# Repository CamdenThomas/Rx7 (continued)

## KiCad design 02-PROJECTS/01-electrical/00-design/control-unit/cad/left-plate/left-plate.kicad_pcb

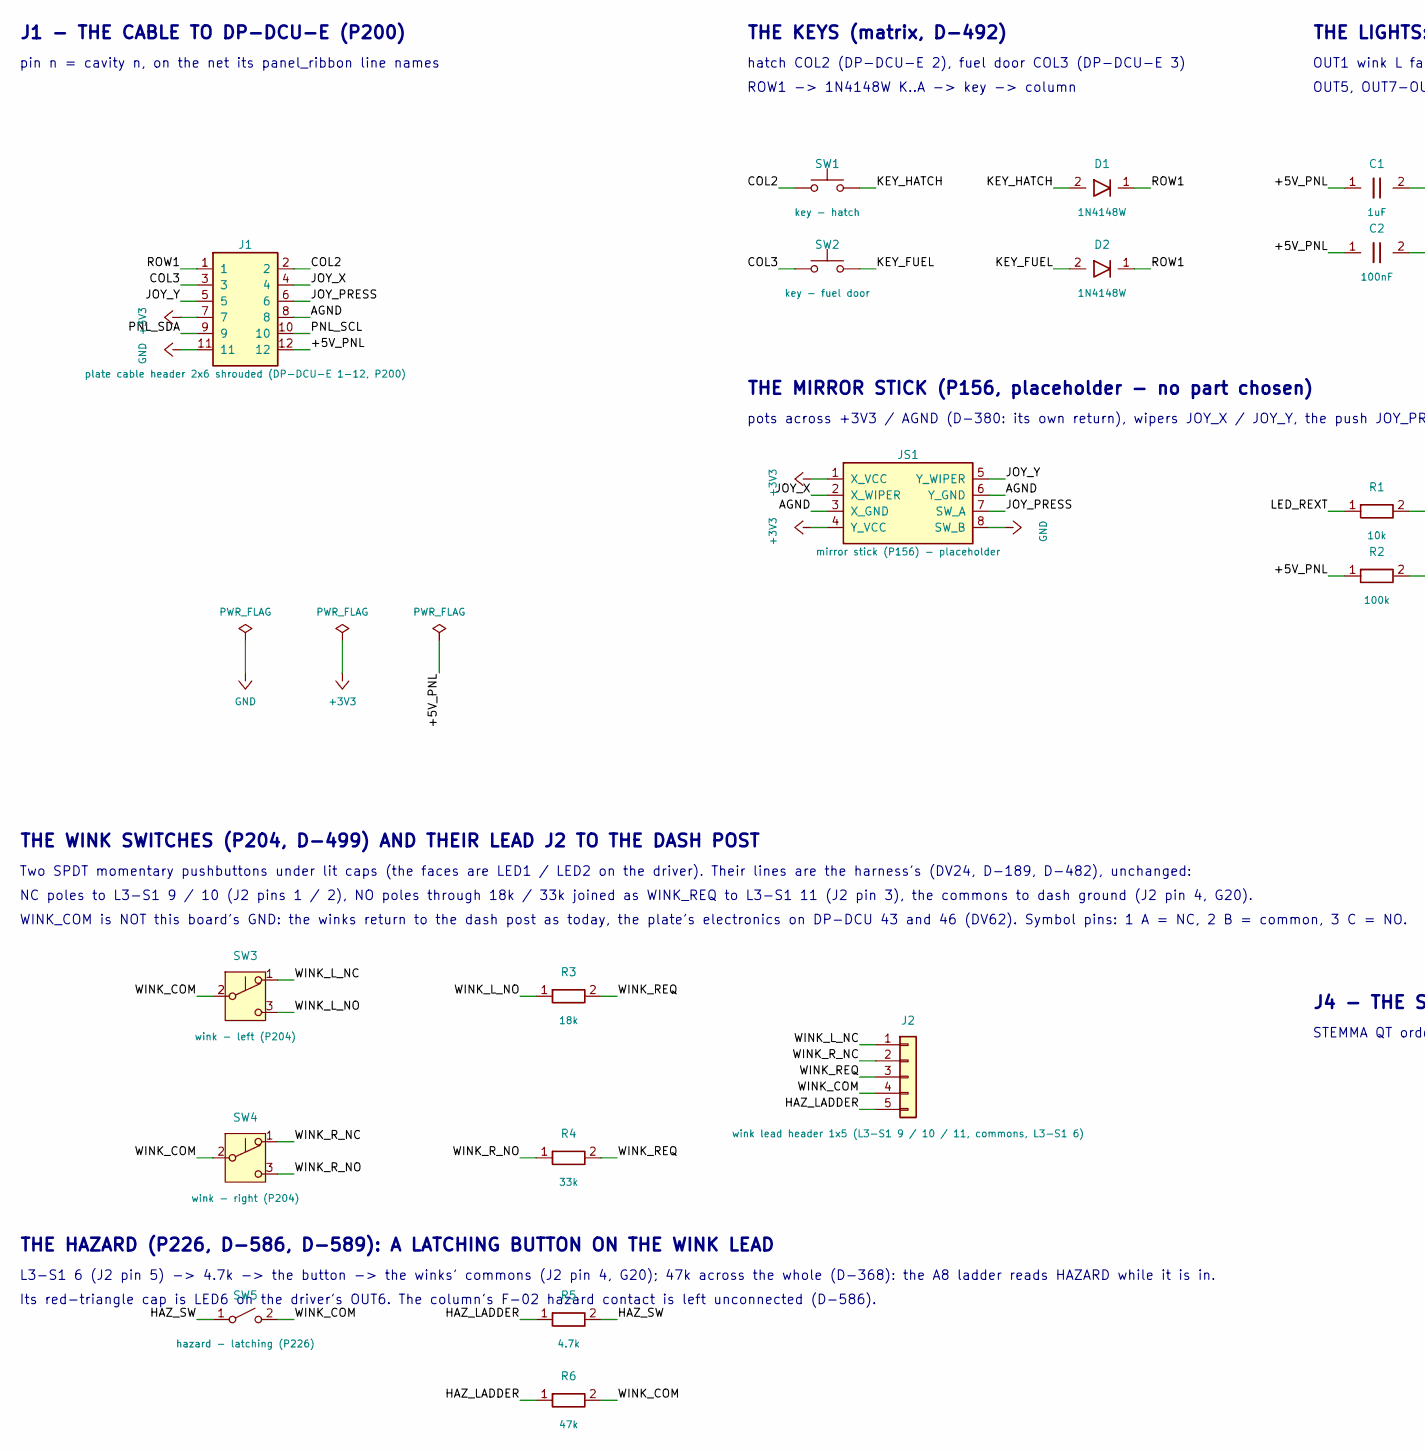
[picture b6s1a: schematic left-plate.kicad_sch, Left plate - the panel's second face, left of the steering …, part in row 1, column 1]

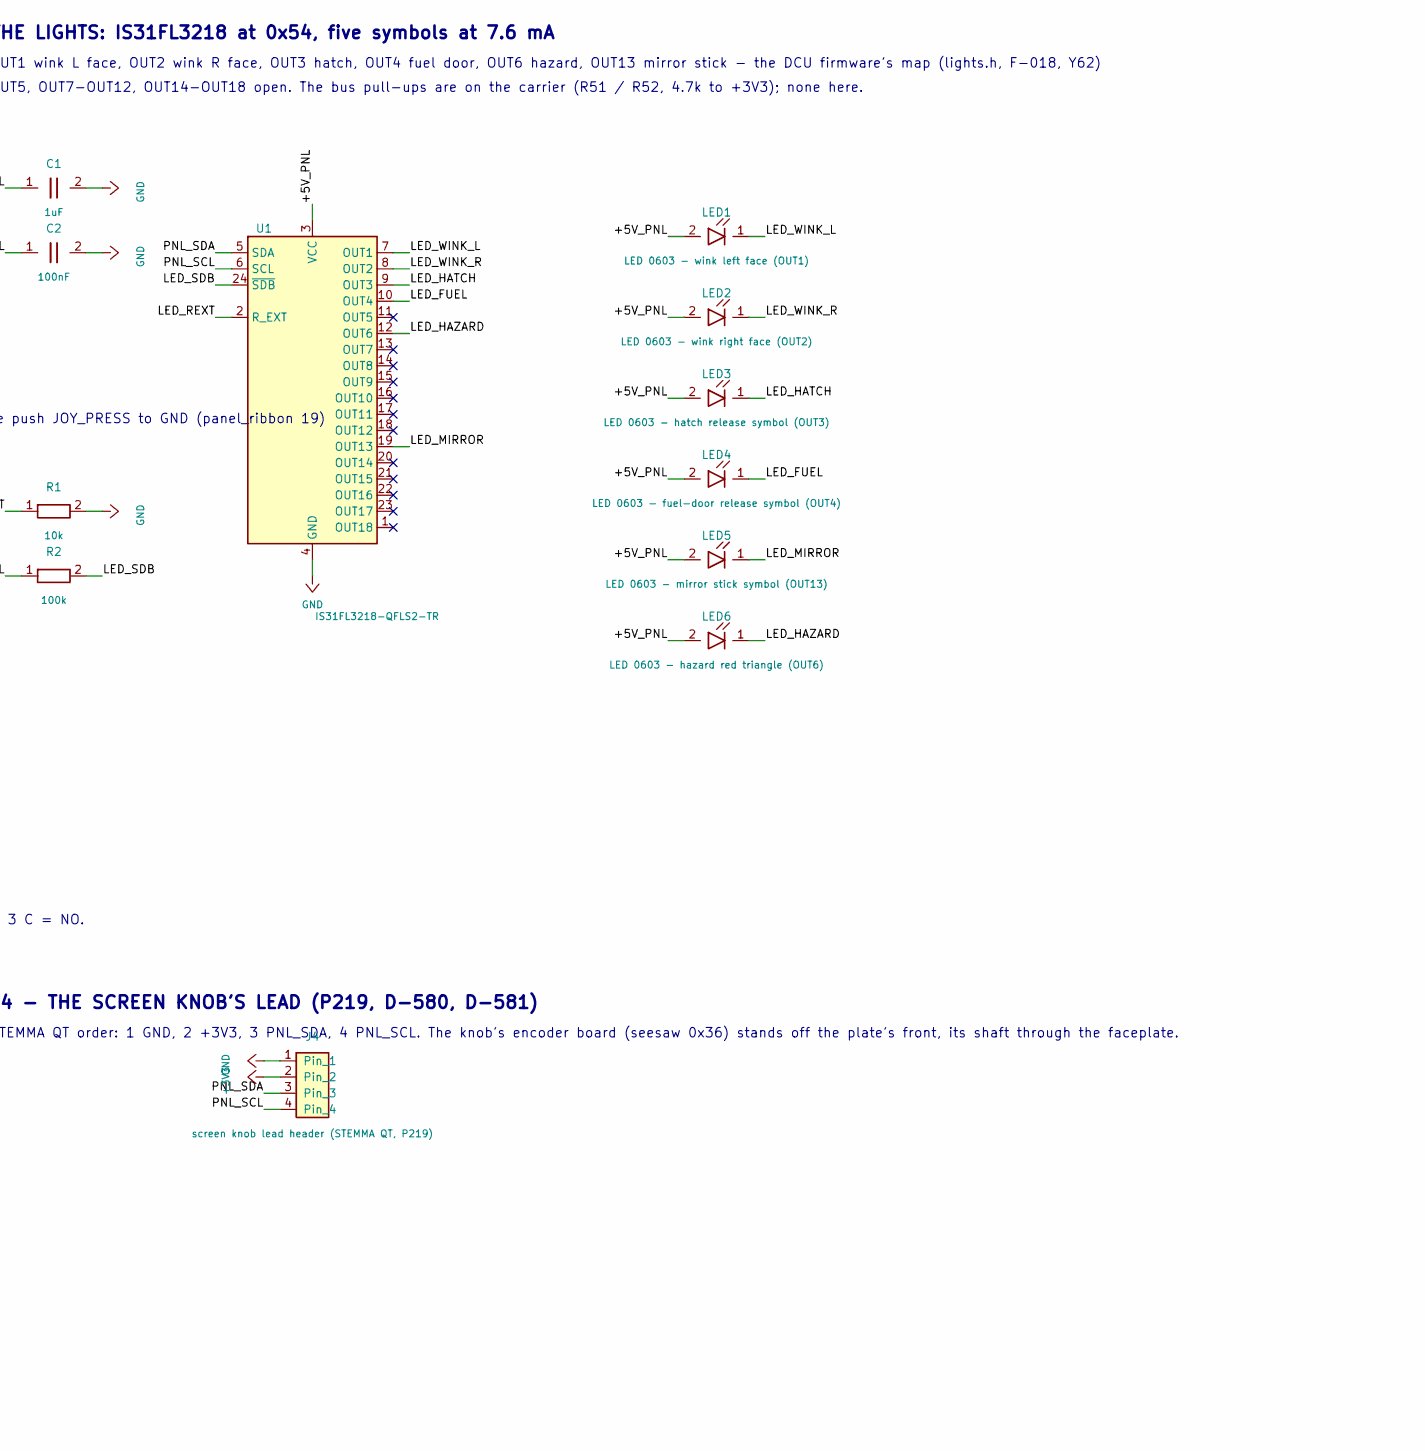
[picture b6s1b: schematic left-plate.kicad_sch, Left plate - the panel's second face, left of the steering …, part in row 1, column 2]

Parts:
C1: 1uF; C_0603_1608Metric
C2: 100nF; C_0603_1608Metric
D1, D2: 1N4148W; D_SOD-123
J1: plate cable header 2x6 shrouded (DP-DCU-E 1-12, P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; IDC-Header_2x06_P2.54mm_Vertical
J2: wink lead header 1x5 (L3-S1 9 / 10 / 11, commons,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; JST_XH_B5B-XH-A_1x05_P2.50mm_Vertical
J4: screen knob lead header (STEMMA QT, P219); JST_SH_BM04B-SRSS-TB_1x04-1MP_P1.00mm_Vertical
JS1: mirror stick (P156) - placeholder; Thumbstick_P156_Placeholder_2x04_P2.54mm
LED1: LED 0603 - wink left face (OUT1); LED_0603_1608Metric
LED2: LED 0603 - wink right face (OUT2); LED_0603_1608Metric
LED3: LED 0603 - hatch release symbol (OUT3); LED_0603_1608Metric
LED4: LED 0603 - fuel-door release symbol (OUT4); LED_0603_1608Metric
LED5: LED 0603 - mirror stick symbol (OUT13); LED_0603_1608Metric
LED6: LED 0603 - hazard red triangle (OUT6); LED_0603_1608Metric
R1: 10k; R_0603_1608Metric
R2: 100k; R_0603_1608Metric
R3: 18k; R_0603_1608Metric
R4: 33k; R_0603_1608Metric
R5: 4.7k; R_0603_1608Metric
R6: 47k; R_0603_1608Metric
SW1: key - hatch; SW_PUSH_6mm
SW2: key - fuel door; SW_PUSH_6mm
SW3: wink - left (P204); WinkSwitch_P204_SPDT_Placeholder
SW4: wink - right (P204); WinkSwitch_P204_SPDT_Placeholder
SW5: hazard - latching (P226); HazardSwitch_P226_Latching_Placeholder
U1: IS31FL3218-QFLS2-TR; QFN-24-1EP_4x4mm_P0.5mm_EP2.7x2.7mm

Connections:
+3V3: J1.7, J4.2, JS1.1 (X_VCC), JS1.4 (Y_VCC)
/+5V_PNL: C1.1, C2.1, J1.12, LED1.2 (A), LED2.2 (A), LED3.2 (A), LED4.2 (A), LED5.2 (A), LED6.2 (A), R2.1, U1.3 (VCC)
/AGND: J1.8, JS1.3 (X_GND), JS1.6 (Y_GND)
/COL2: J1.2, SW1.1
/COL3: J1.3, SW2.1
/HAZ_LADDER: J2.5, R5.1, R6.1
/HAZ_SW: R5.2, SW5.1 (A)
/JOY_PRESS: J1.6, JS1.7 (SW_A)
/JOY_X: J1.4, JS1.2 (X_WIPER)
/JOY_Y: J1.5, JS1.5 (Y_WIPER)
/KEY_FUEL: D2.2 (A), SW2.2
/KEY_HATCH: D1.2 (A), SW1.2
/LED_FUEL: LED4.1 (K), U1.10 (OUT4)
/LED_HATCH: LED3.1 (K), U1.9 (OUT3)
/LED_HAZARD: LED6.1 (K), U1.12 (OUT6)
/LED_MIRROR: LED5.1 (K), U1.19 (OUT13)
/LED_REXT: R1.1, U1.2 (R_EXT)
/LED_SDB: R2.2, U1.24 (~SDB)
/LED_WINK_L: LED1.1 (K), U1.7 (OUT1)
/LED_WINK_R: LED2.1 (K), U1.8 (OUT2)
/PNL_SCL: J1.10, J4.4, U1.6 (SCL)
/PNL_SDA: J1.9, J4.3, U1.5 (SDA)
/ROW1: D1.1 (K), D2.1 (K), J1.1
/WINK_COM: J2.4, R6.2, SW3.2 (B), SW4.2 (B), SW5.2 (B)
/WINK_L_NC: J2.1, SW3.1 (A)
/WINK_L_NO: R3.1, SW3.3 (C)
/WINK_REQ: J2.3, R3.2, R4.2
/WINK_R_NC: J2.2, SW4.1 (A)
/WINK_R_NO: R4.1, SW4.3 (C)
GND: C1.2, C2.2, J1.11, J4.1, JS1.8 (SW_B), R1.2, U1.4 (GND), U1.25 (GND)

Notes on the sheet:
J1 - THE CABLE TO DP-DCU-E (P200)
pin n = cavity n, on the net its panel_ribbon line names
THE KEYS (matrix, D-492)
ROW1 -> 1N4148W K..A -> key -> column
hatch COL2 (DP-DCU-E 2), fuel door COL3 (DP-DCU-E 3)
THE MIRROR STICK (P156, placeholder - no part chosen)
pots across +3V3 / AGND (D-380: its own return), wipers JOY_X / JOY_Y, the push JOY_PRESS to GND (panel_ribbon 19)
THE LIGHTS: IS31FL3218 at 0x54, five symbols at 7.6 mA
OUT1 wink L face, OUT2 wink R face, OUT3 hatch, OUT4 fuel door, OUT6 hazard, OUT13 mirror stick - the DCU firmware's map (lights.h, F-018, Y62)
OUT5, OUT7-OUT12, OUT14-OUT18 open. The bus pull-ups are on the carrier (R51 / R52, 4.7k to +3V3); none here.
THE WINK SWITCHES (P204, D-499) AND THEIR LEAD J2 TO THE DASH POST
Two SPDT momentary pushbuttons under lit caps (the faces are LED1 / LED2 on the driver). Their lines are the harness's (DV24, D-189, D-482), unchanged:
NC poles to L3-S1 9 / 10 (J2 pins 1 / 2), NO poles through 18k / 33k joined as WINK_REQ to L3-S1 11 (J2 pin 3), the commons to dash ground (J2 pin 4, G20).
WINK_COM is NOT this board's GND: the winks return to the dash post as today, the plate's electronics on DP-DCU 43 and 46 (DV62). Symbol pins: 1 A = NC, 2 B = common, 3 C = NO.
THE HAZARD (P226, D-586, D-589): A LATCHING BUTTON ON THE WINK LEAD
L3-S1 6 (J2 pin 5) -> 4.7k -> the button -> the winks' commons (J2 pin 4, G20); 47k across the whole (D-368): the A8 ladder reads HAZARD while it is in.
Its red-triangle cap is LED6 on the driver's OUT6. The column's F-02 hazard contact is left unconnected (D-586).
J4 - THE SCREEN KNOB'S LEAD (P219, D-580, D-581)
STEMMA QT order: 1 GND, 2 +3V3, 3 PNL_SDA, 4 PNL_SCL. The knob's encoder board (seesaw 0x36) stands off the plate's front, its shaft through the faceplate.

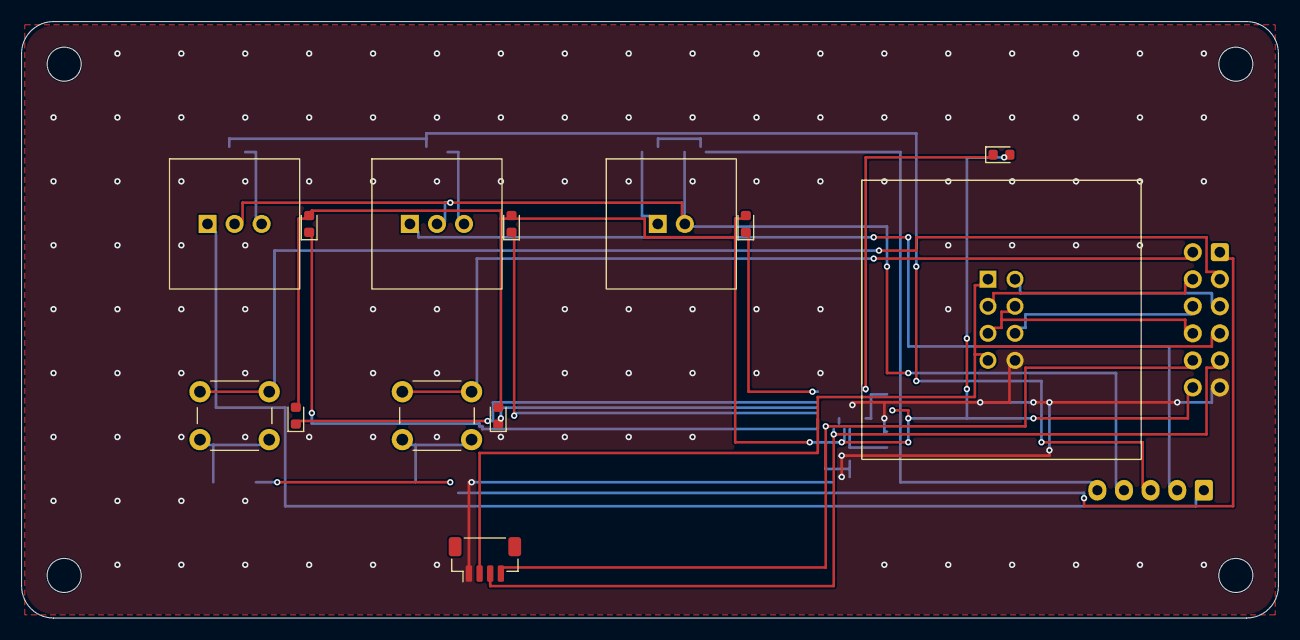
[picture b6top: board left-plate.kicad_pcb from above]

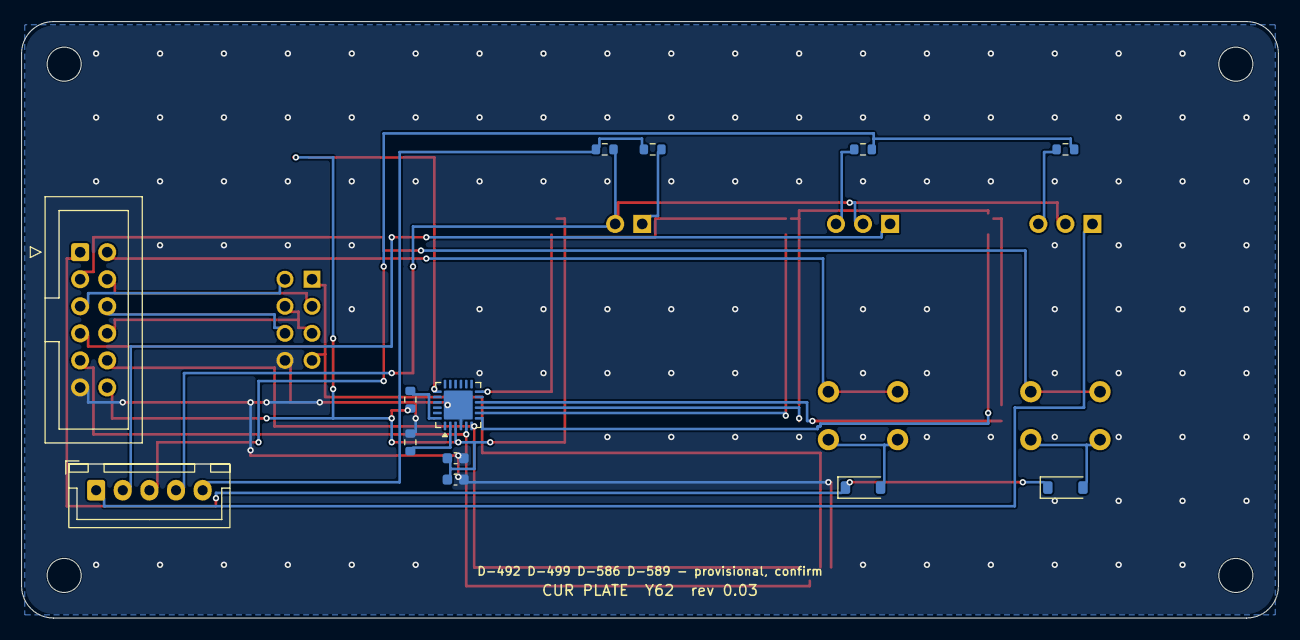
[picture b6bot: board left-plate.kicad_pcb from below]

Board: 2 copper layers, 118.0 x 56.0 mm, 31 parts (13 on the bottom side), 30 nets.

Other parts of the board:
H1, H2, H3, H4: M3; MountingHole_3.2mm_M3
KN1: screen knob board (P219); ScreenKnob_P219_Board_Placeholder

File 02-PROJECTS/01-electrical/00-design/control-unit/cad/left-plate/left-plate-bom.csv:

"Refs","Value","Footprint","Qty","DNP"
"C1","1uF","Capacitor_SMD:C_0603_1608Metric","1",""
"C2","100nF","Capacitor_SMD:C_0603_1608Metric","1",""
"D1","1N4148W","Diode_SMD:D_SOD-123","1",""
"D2","1N4148W","Diode_SMD:D_SOD-123","1",""
"J1","plate cable header 2x6 shrouded (DP-DCU-E 1-12, P200)","Connector_IDC:IDC-Header_2x06_P2.54mm_Vertical","1",""
"J2","wink lead header 1x5 (L3-S1 9 / 10 / 11, commons, L3-S1 6)","Connector_JST:JST_XH_B5B-XH-A_1x05_P2.50mm_Vertical","1",""
"J4","screen knob lead header (STEMMA QT, P219)","Connector_JST:JST_SH_BM04B-SRSS-TB_1x04-1MP_P1.00mm_Vertical","1",""
"JS1","mirror stick (P156) - placeholder","left-plate:Thumbstick_P156_Placeholder_2x04_P2.54mm","1",""
"LED1","LED 0603 - wink left face (OUT1)","LED_SMD:LED_0603_1608Metric","1",""
"LED2","LED 0603 - wink right face (OUT2)","LED_SMD:LED_0603_1608Metric","1",""
"LED3","LED 0603 - hatch release symbol (OUT3)","LED_SMD:LED_0603_1608Metric","1",""
"LED4","LED 0603 - fuel-door release symbol (OUT4)","LED_SMD:LED_0603_1608Metric","1",""
"LED5","LED 0603 - mirror stick symbol (OUT13)","LED_SMD:LED_0603_1608Metric","1",""
"LED6","LED 0603 - hazard red triangle (OUT6)","LED_SMD:LED_0603_1608Metric","1",""
"R1","10k","Resistor_SMD:R_0603_1608Metric","1",""
"R2","100k","Resistor_SMD:R_0603_1608Metric","1",""
"R3","18k","Resistor_SMD:R_0603_1608Metric","1",""
"R4","33k","Resistor_SMD:R_0603_1608Metric","1",""
"R5","4.7k","Resistor_SMD:R_0603_1608Metric","1",""
"R6","47k","Resistor_SMD:R_0603_1608Metric","1",""
"SW1","key - hatch","Button_Switch_THT:SW_PUSH_6mm","1",""
"SW2","key - fuel door","Button_Switch_THT:SW_PUSH_6mm","1",""
"SW3","wink - left (P204)","left-plate:WinkSwitch_P204_SPDT_Placeholder","1",""
"SW4","wink - right (P204)","left-plate:WinkSwitch_P204_SPDT_Placeholder","1",""
"SW5","hazard - latching (P226)","left-plate:HazardSwitch_P226_Latching_Placeholder","1",""
"U1","IS31FL3218-QFLS2-TR","Package_DFN_QFN:QFN-24-1EP_4x4mm_P0.5mm_EP2.7x2.7mm","1",""
